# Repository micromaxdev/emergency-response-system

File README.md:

# Emergency Response System (ERS)

A LoRa-based emergency alerting system developed through ECTE351 and extended
in‑house. Battery‑powered **Pi Pico / LoRa terminal devices** send emergency
triggers to a **Raspberry Pi backend server**, which fans each alert out to
audio sirens, a relay (mass‑notification siren), email and SMS, and records every
incident in a SQLite database. A **Streamlit dashboard** provides live monitoring,
staff/device management, logs and configuration.

> Location estimation (RSSI trilateration) and the BLE gateway tooling are
> **experimental** and under active development.

## Architecture

```
emergency-response-system/
├── server/                     Raspberry Pi backend (TCP listener + alert fan‑out)
│   ├── server.py               Entry point  →  python3 server/server.py
│   ├── config.py               Paths, host/port, constants
│   ├── event_log.py            JSONL event logger
│   ├── database.py             SQLite schema, control flags, incidents, lookups
│   ├── incident_handler.py     Payload → alerts (audio/email/sms/relay) + DB record
│   ├── alert_runtime.py        Background relay/audio siren loops
│   ├── tcp_server.py           Listening socket
│   ├── location.py             Optional RSSI trilateration wrapper (experimental)
│   ├── alert_handlers/         Pluggable alerts: email_alert, sms_alert, audio_alert, relay_alert
│   ├── trilateration.py        RSSI→distance + 2D trilateration (experimental)
│   ├── ble_gateway_*.py        BLE/MQTT gateway listener & calibration (experimental)
│   └── *_test.py               Localisation test scripts (experimental)
├── websites/                   Streamlit dashboard
│   ├── web_main.py             Entry point  →  streamlit run websites/web_main.py
│   ├── utils/                  Shared package: config, styles, db, incidents, staff,
│   │                           devices, battery, system, mapping, heartbeat
│   └── pages/                  Home, Dashboard, Configuration, Staff, Logs, Battery, Emergency
├── client/                     Pi Pico / LoRa terminal firmware (MicroPython) + SX126x drivers
├── assets/
│   ├── maps/                   Floor plans
│   └── audios/                 Alert sound files (mass / personal)
├── data/                       ers.sqlite — runtime database (created on first run)
├── logs/                       emergency_log.jsonl — runtime event log
├── requirements.txt
└── README.md
```

The server and the dashboard run as **two separate processes** and communicate
only through the shared SQLite database (`data/ers.sqlite`) and a small TCP
command channel (the dashboard tells the server to stop sirens, etc.).

## Prerequisites

- **Python 3.10+**
- Python packages: `pip install -r requirements.txt`
- **Audio playback** (server host): `ffplay` (from FFmpeg) preferred, or `mpg123`.
- **Relay HAT** (Raspberry Pi only): I²C enabled (`raspi-config`); the `smbus2`
  package drives the relay over I²C address `0x10`.

### Environment variables

Alert handlers read credentials from `~/.env`:

```ini
# Email (SMTP)
EMAIL_HOST=smtp.example.com
EMAIL_PORT=587
EMAIL_ADDRESS=alerts@example.com
EMAIL_PASSWORD=app-password
EMAIL_TO=fallback@example.com        # optional default recipients (comma-separated)

# SMS (Twilio)
TWILIO_ACCOUNT_SID=ACxxxxxxxx
TWILIO_AUTH_TOKEN=xxxxxxxx
TWILIO_MESSAGING_SERVICE_SID=MGxxxxxxxx
SMS_TO=+61400000000                  # optional default recipient(s)
```

Per‑incident email/SMS recipients are normally taken from the **staff** table
(managed on the dashboard); the `EMAIL_TO` / `SMS_TO` values are fallbacks.

## Running

From the project root:

```bash
# 1. (first time) create and activate a virtual environment, install deps
python3 -m venv venv
source venv/bin/activate
pip install -r requirements.txt

# 2. Start the backend server — listens on TCP :8081 for device payloads
python3 server/server.py

# 3. In a second shell, start the dashboard
python3 -m streamlit run websites/web_main.py
```

`server/server.py` creates the database schema on startup. Relay and audio
sirens, once triggered by a mass emergency, loop until stopped from the
dashboard.

### Sending a test payload

```bash
printf '{"device_id":"PICO1","emergency":true,"emergency_type":"mass","emergency_message":"TEST"}' \
  | nc <server-ip> 8081
```

This should produce a log line in `logs/emergency_log.jsonl`, a new row in the
`incidents` table, and (on a configured Pi) audio + relay activation. Send
`{"command":"stop_alerts"}` to silence them.

## Experimental: location & BLE

The localisation features are not yet production‑ready:

- `server/trilateration.py` — RSSI→distance and 2D trilateration maths.
- `server/location.py` — wraps trilateration into the incident pipeline; only runs
  when a payload includes a `gateways` array.
- `server/ble_gateway_listener.py`, `server/ble_gateway_calibrate.py`,
  `server/cal_data.json` — BLE/MQTT gateway listener, live position plot and
  RSSI calibration. These need extra packages: `paho-mqtt`, `scipy`, `matplotlib`.
- `server/*_test.py` — standalone scripts for exploring the localisation maths.

## Notes

- Hardware design files (`schematics/`) and the compiled LoRa concentrator HAL
  (`sx1302_hal_rpi5-master/`) are kept on the deployment machine but are not
  tracked in version control.

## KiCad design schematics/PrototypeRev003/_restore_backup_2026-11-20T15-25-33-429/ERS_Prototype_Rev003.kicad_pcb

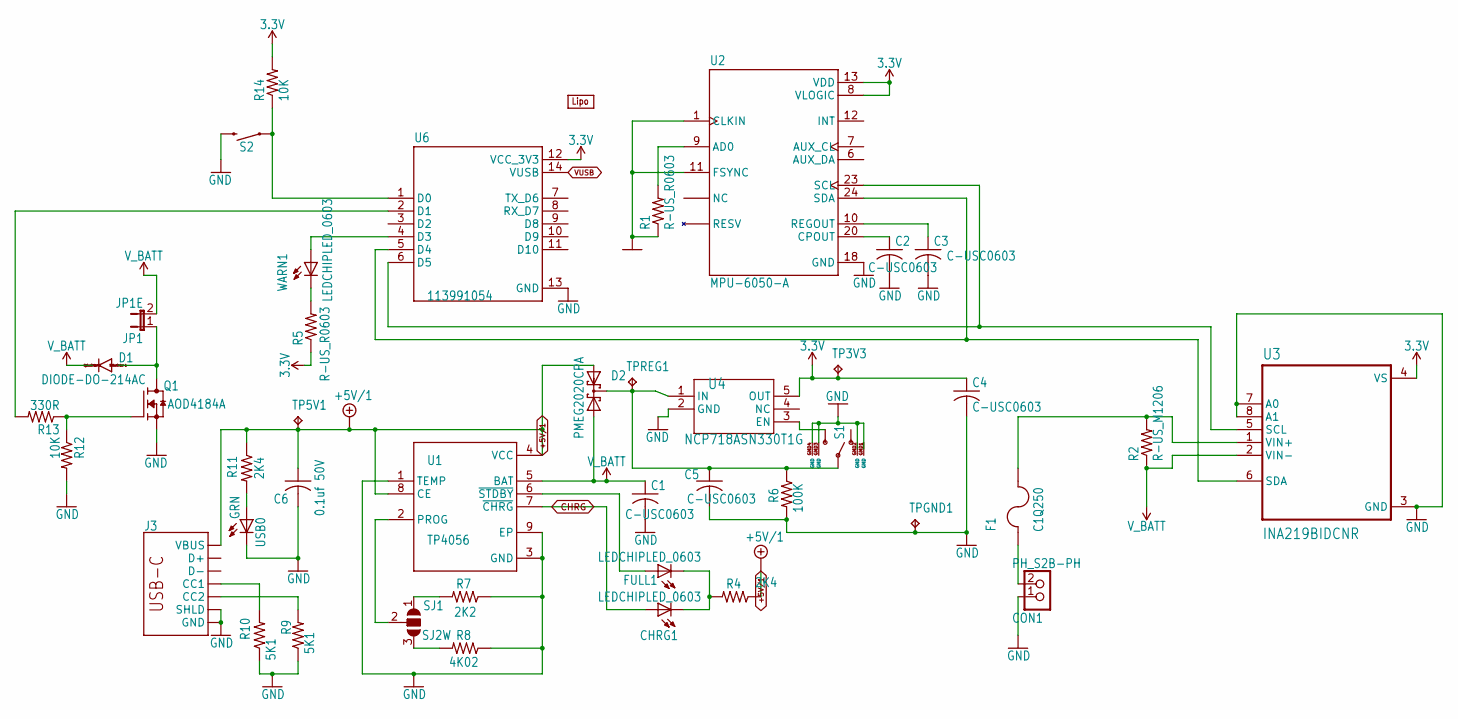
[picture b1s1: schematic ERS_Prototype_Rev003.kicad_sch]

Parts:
BT1: LIPO-OUTLINE1000; LIPO-1000
C1, C2, C3, C4, C5: C-USC0603; C0603
C6: 0.1uf 50V; C0805
CHRG1: LEDCHIPLED_0603; CHIPLED_0603
CON1: PH_S2B-PH; S2B-PH
D1: DIODE-DO-214AC; DO-214AC
D2: PMEG2020CPA; SOT1061
F1: C1Q250; MPN C1Q 250; DIGIKEY_PARTNO 507-1073-1-ND
FULL1: LEDCHIPLED_0603; CHIPLED_0603
J3: USB Female Type C Connector; USB-C-16P-4LAYER-ISOLATED
JP1: JP1E; JP1
Q1: AOD4184A; DPAK228P994X240-4N
R1, R5: R-US_R0603; R0603
R2: R-US_M1206; M1206
R4, R11: 2K4; R0603
R6: 100K; R0603
R7: 2K2; R0603
R8: 4K02; R0603
R9, R10: 5K1; R0603
R12, R14: 10K; R0603
R13: 330R; R0603
S1: SWITCH-SPDT-SMD-RIGHT-ANGLE; SWITCH_SPST_SMD_A
S2: MOMENTARY-SWITCH-SPST-PTH-12MM; TACTILE_SWITCH_PTH_12MM
SJ1: SJ2W; SJ_2
TP3V3, TP5V1: TPB1,27; B1,27
TPGND1: TPB1,27; B1,27
TPREG1: TPB1,27; B1,27
U1: TP4056; SOP127P600X175-9N
U2: MPU-6050-A; QFN50P400X400X95-24N
U3: INA219BIDCNR; SOT65P280X145-8N
U4: NCP718ASN330T1G; TSOT23-5_ONS
U6: 113991054; MODULE_113991054
USB0: GRN; CHIPLED_0805
WARN1: LEDCHIPLED_0603; CHIPLED_0603

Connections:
3.3V: C4.1, R5.1, R14.2, TP3V3.TP (TP_TP), U2.8 (VLOGIC), U2.13 (VDD), U3.4 (VS), U4.5 (OUT), U6.12 (VCC_3V3)
+5V/1: C6.1, D2.1 (A1), J3.VBUS1 (VBUS), J3.VBUS2 (VBUS), R4.1, R11.1, TP5V1.TP (TP_TP), U1.4 (VCC), U1.8 (CE)
CHRG: CHRG1.A, U1.7 (~CHRG)
GND: C1.2, C2.2, C3.2, C4.2, C5.2, C6.2, CON1.1, J3.GND, J3.GND2 (GND), J3.SHLD1 (SHLD), J3.SHLD2 (SHLD), J3.SHLD3 (SHLD), J3.SHLD4 (SHLD), J3.SHLD5 (SHLD), J3.SHLD6 (SHLD), J3.SHLD7 (SHLD), J3.SHLD8 (SHLD), Q1.3 (S), R1.1, R6.2, R7.1, R8.1, R9.1, R10.1, R12.2, S1.GND3 (GND), S1.GND4 (GND), S2.3 (2), TPGND1.TP (TP_TP), U1.1 (TEMP), U1.3 (GND), U1.9 (EP), U2.1 (CLKIN), U2.11 (FSYNC), U2.18 (GND), U3.3 (GND), U3.7 (A0), U3.8 (A1), U4.2 (GND), U6.13 (GND), USB0.C
unnamed: CHRG1.C, FULL1.C, R4.2
unnamed: CON1.2, F1.1
unnamed: C5.1, D2.3 (K1K2), R6.1, S1.2, TPREG1.TP (TP_TP), U4.1 (IN)
unnamed: J3.A5 (CC1), R10.2
unnamed: J3.B5 (CC2), R9.2
unnamed: J3.A6 (D+), J3.B6 (D+)
unnamed: J3.A7 (D-), J3.B7 (D-)
unnamed: D1.A, JP1.1, Q1.4 (D)
unnamed: Q1.1 (G), R12.1, R13.1
unnamed: R5.2, WARN1.C
unnamed: R7.2, SJ1.1
unnamed: R8.2, SJ1.3
unnamed: R11.2, USB0.A
unnamed: S1.3 (S), U4.3 (EN)
unnamed: SJ1.2, U1.2 (PROG)
unnamed: FULL1.A, U1.6 (~STDBY)
unnamed: R1.2, U2.9 (AD0)
unnamed: C2.1, U2.20 (CPOUT)
unnamed: U2.2 (NC), U2.3 (NC), U2.4 (NC), U2.5 (NC), U2.14 (NC), U2.15 (NC), U2.16 (NC), U2.17 (NC)
unnamed: C3.1, U2.10 (REGOUT)
unnamed: U2.23 (SCL), U3.5 (SCL), U6.6 (D5)
unnamed: U2.24 (SDA), U3.6 (SDA), U6.5 (D4)
unnamed: F1.2, R2.2, U3.1 (VIN+)
unnamed: R14.1, S2.1, U6.1 (D0)
unnamed: R13.2, U6.2 (D1)
unnamed: U6.4 (D3), WARN1.A
VUSB: U6.14 (VUSB)
V_BATT: C1.1, D1.C, D2.2 (A2), JP1.2, R2.1, U1.5 (BAT), U3.2 (VIN-)

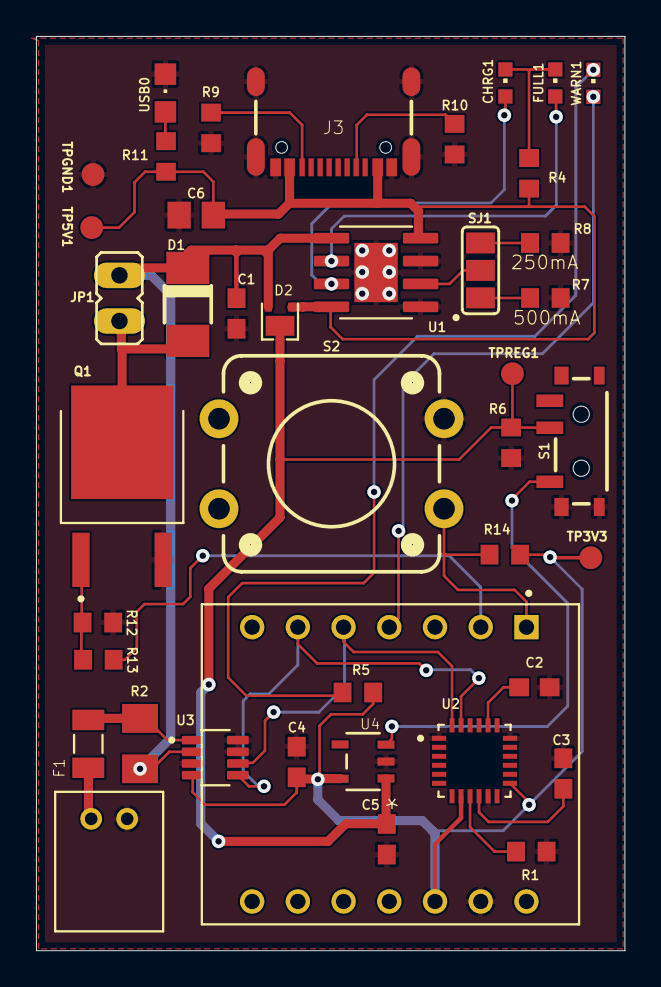
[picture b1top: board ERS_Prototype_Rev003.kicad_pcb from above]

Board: 2 copper layers, 32.7 x 50.8 mm, 43 parts (0 on the bottom side), 31 nets.

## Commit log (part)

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2026-02-05 Add instructions for server code file organization
2026-02-05 Add instructions for client side code organization
2026-02-05 Add instructions for 3D model file placement
2026-02-05 Add instructions for circuit design files
2026-02-05 Add files via upload
    Client Side Device Code with working Mass Emergency Button(5 presses), Personal Emergency Button(5 Second Hold), Fall detection thread and a cancel button for falls that do not require assistance.
2026-02-05 Refactor emergency script for Pico W
2026-02-06 test
2026-02-11 Server Update
    Email, SMS, Relay and Audio outputs
2026-03-05 Traffic Counter Schematic
2026-03-18 Added all alerts to their own folder
2026-03-19 Seeed nRF Ble advertise code
2026-03-19 Added main server file
2026-03-19 sqlite
2026-03-19 Refactored server code
2026-03-30 Skylar's changes
2026-04-27 Everything except BLE location
2026-04-28 client device with lora functionality code
2026-04-28 Restore all files except secrets
2026-05-11 configure of map
2026-05-14 ble gateway config
2026-06-05 client
2026-06-09 Add server modules & website utils; remove artifacts
    Introduce core server components and website utilities, overhaul README, and clean repository noise. Added server modules (config.py, database.py, event_log.py, incident_handler.py, alert_runtime.py,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
2026-06-22 Location attempts
2026-06-22 Cleaned client
2026-06-23 added schematic
2026-06-23 email alert
2026-06-24 Email alerts
2026-06-24 Test files separation
2026-06-24 3d Models
2026-06-25 renamed website
2026-06-25 website update: new styles
